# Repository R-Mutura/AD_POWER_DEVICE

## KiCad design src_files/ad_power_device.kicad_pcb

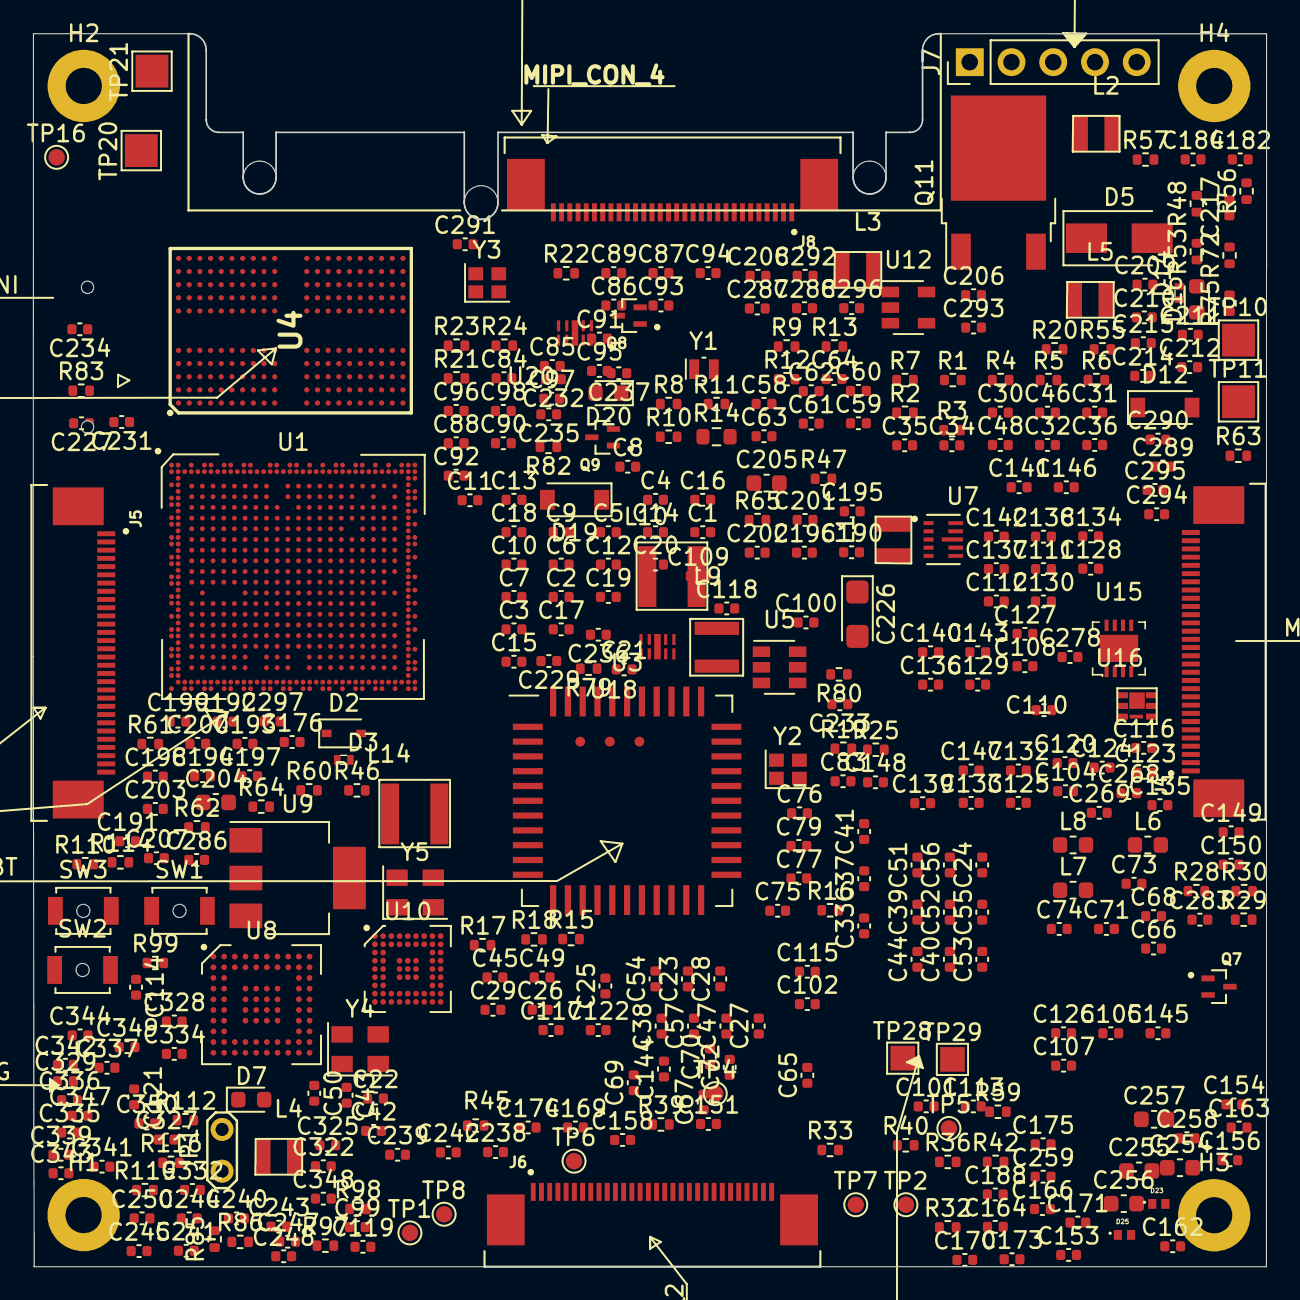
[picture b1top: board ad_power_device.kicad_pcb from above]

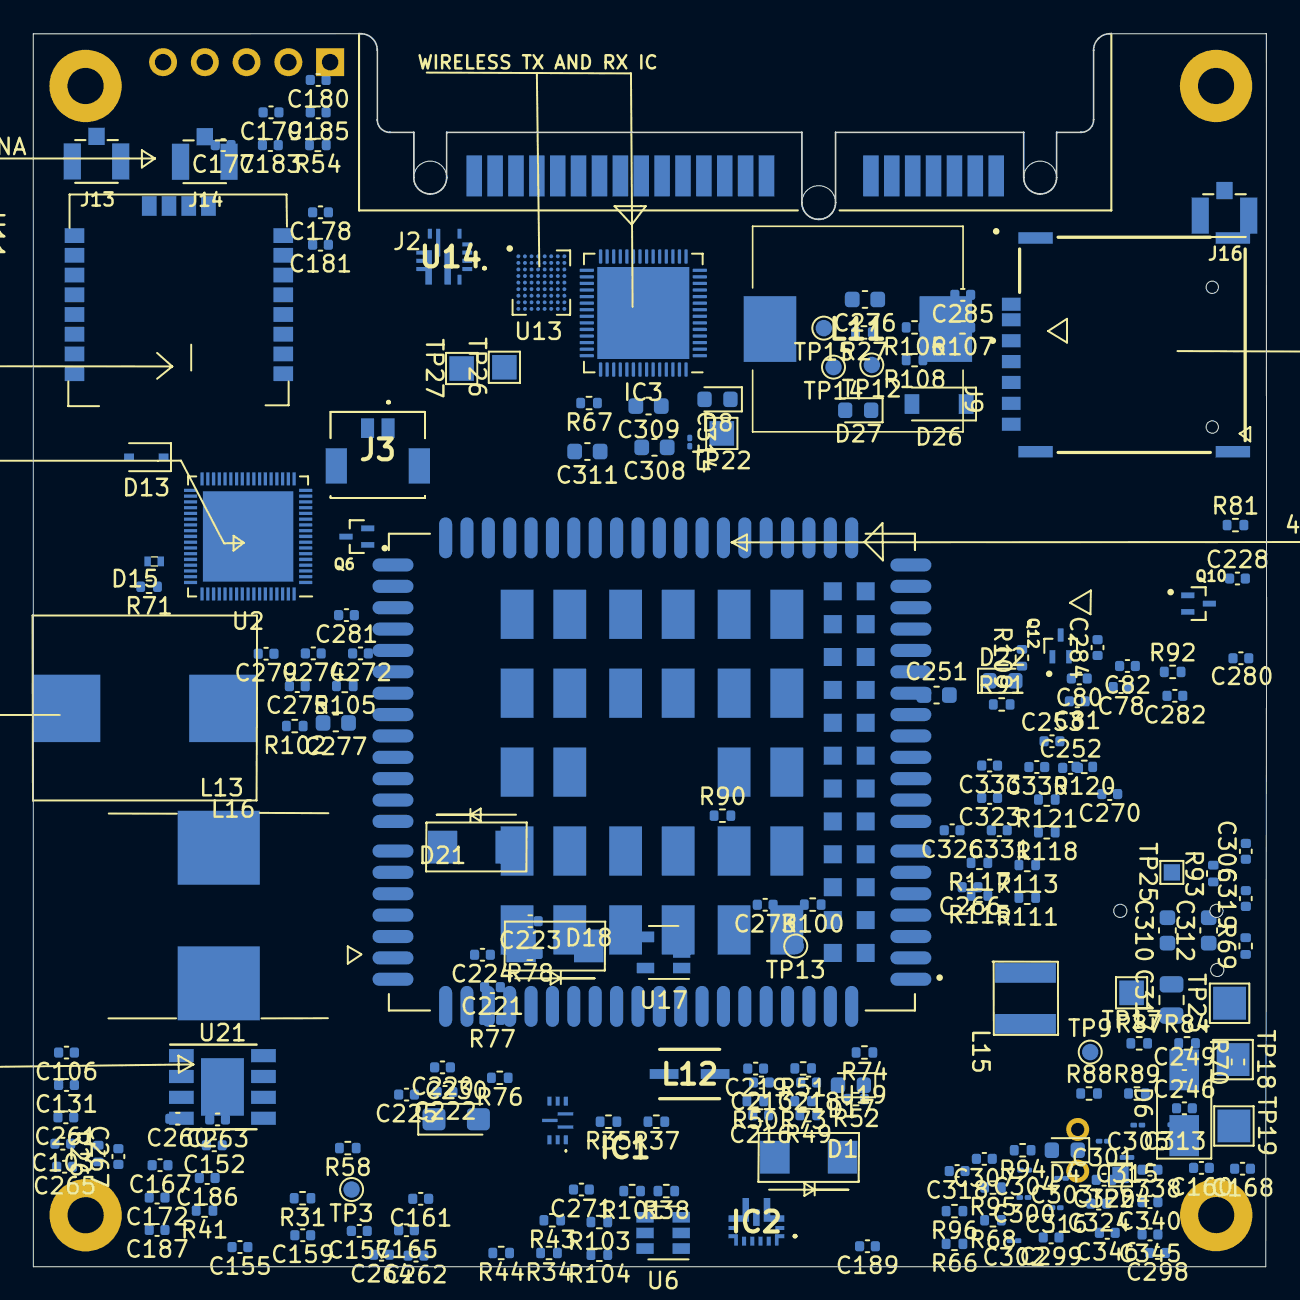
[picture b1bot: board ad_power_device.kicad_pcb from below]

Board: 2 copper layers, 75.0 x 75.0 mm, 593 parts (207 on the bottom side), 373 nets, no tracks yet.

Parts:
C1, C2, C5, C6, C15, C17, C18, C19, C21, C23, C24, C29, C30, C36, C48, C49, C99, C101, C122, C124, C149, C150, C222, C223, C224, C225, C283: 22uF; C_0402_1005Metric
C3, C4, C20, C31, C32, C35, C38, C39, C45, C46, C55, C79, C81, C96, C100, C102, C104, C106, C109, C131, C146, C148, C164, C165, C167, C169, C220, C221, C270, C280, C281, C282, C298, C306, C307, C332, C335, C339: 10uF; C_0402_1005Metric
C7, C10, C12, C13, C14, C16, C51, C83, C94, C95, C97, C107, C151, C152, C184, C186, C187, C239, C242, C279: 4.7uF; C_0402_1005Metric
C8, C9, C11, C63, C64, C78, C80, C82, C86, C87, C88, C89, C90, C91, C92, C93, C103, C105, C110, C112, C113, C114, C115, C116, C117, C118, C119, C120, C121, C123, C125, C126, C127, C128, C129, C130, C132, C133, C134, C135, C136, C137, C138, C139, C140, C141, C142, C143, C144, C145, C147, C157, C158, C159, C160, C161, C162, C163, C166, C168, C170, C171, C172, C173, C174, C175, C177, C183, C185, C188, C189, C190, C192, C193, C194, C195, C196, C197, C198, C199, C200, C201, C202, C208, C211, C212, C215, C216, C217, C218, C227, C231, C236, C238, C240, C241, C243, C244, C245, C250, C258, C259, C260, C261, C262, C263, C264, C265, C266, C267, C271, C278, C286, C287, C288, C289, C290, C291, C292, C293, C294, C297, C318, C319, C325, C329, C331, C344, C345, C346, C347: 100nF; C_0402_1005Metric
C22, C27, C28, C33, C34, C40, C41, C42, C43, C44, C47, C50, C52, C54, C61, C62, C67, C69, C70, C108, C111, C153, C154, C155, C156, C176, C206, C209, C210, C213, C214, C219, C252, C253, C295, C296, C322, C324, C326, C328: 1uF; C_0402_1005Metric
C25, C26, C53, C60: 100n; C_0402_1005Metric
C37, C56, C57: 10u; C_0402_1005Metric
C58, C59: 22pF; C_0402_1005Metric
C65: 10uF_10V; C_0402_1005Metric
C66, C68, C273: 2.2uF; C_0402_1005Metric
C71, C72: 100nF_10V; C_0402_1005Metric
C73, C74, C246, C247, C248, C249: 1nF_50V; C_0402_1005Metric
C75, C76: 12pF; C_0402_1005Metric
C77: 9pF; C_0402_1005Metric
C84, C85: 18pF; C_0402_1005Metric
C98, C336, C343: 1nF; C_0402_1005Metric
C178, C179: 220pF; C_0402_1005Metric
C180, C181: 180pF; C_0402_1005Metric
C182: 66pF; C_0402_1005Metric
C191, C203, C207: 0.1uF; C_0402_1005Metric
C204, C205, C310, C311, C312: 10uF; C_0603_1608Metric
C226, C230: 100uF; CP_EIA-3216-18_Kemet-A
C228, C232, C234, C235, C237: 33pF; C_0402_1005Metric
C229, C233: 10pF; C_0402_1005Metric
C251: 3200pF; C_0603_1608Metric
C254, C255: 47uF_10V; C_0603_1608Metric
C256, C257: 22uF_10V; C_0603_1608Metric
C268, C269: 27pF_50V; C_0402_1005Metric
C272: 100NF; C_0402_1005Metric
C274: 39nF; C_0402_1005Metric
C275: 82pF; C_0402_1005Metric
C276, C277: 22uF_16V; C_0603_1608Metric
C284, C285: 10nF; C_0402_1005Metric
C299: 4.7nF; C_0402_1005Metric
C300, C301: 22nF; C_01005_0402Metric
C302, C303, C304, C305, C313: 47nF; C_01005_0402Metric
C308, C309: 2.2uF; C_0603_1608Metric
C314, C315, C316: 100nF; C_01005_0402Metric
C317: 15uF; C_0805_2012Metric
C320: 100pF; C_0402_1005Metric
C323, C327, C330, C333, C334: 6.8nF; C_0402_1005Metric
C337, C338: 100nF_50V; C_0402_1005Metric
C340, C341, C349: 22nF_50V; C_0402_1005Metric
C342, C348, C350: 3.3nF; C_0402_1005Metric
D1, D18, D21: SS56; SMAG
D2, D13: 1N5819WS; D_SOD-323
D3, D14, D15: ESD5451R-2/TR; DFP1006-2L
D4, D7, D16, D17, D22: LED; LED_0603_1608Metric
D5, D6: SMAJ16A; D_SMA
D8: CDSU400B; D_0603_1608Metric
D12, D19, D26: SMF11A; D_SOD-123
D20, D27: LED_GREEN; LED_0603_1608Metric
D23, D25: ESD9X5VU; ESD9X5VU_DFN1006-2
H1, H2, H3, H4: MountingHole; MountingHole_2.2mm_M2_Pad
IC1: TPS62867RQYR; TPS62865RQYR
IC2: TPS61288RQQR
IC3: P9038; QFN-56-1EP_7x7mm_P0.4mm_EP5.6x5.6mm
J2: 5622-6309-ML; 3M_5622-6309-ML
J3: 205957-0271; 2059570271
J4, J5, J6, J8: 3-1734592-0; TE_3-1734592-0
J7: Conn_01x05_Male; PinHeader_1x05_P2.54mm_Vertical
J9: SIM8066-6-1-14-01-A_REVA; GCT_SIM8066-6-1-14-01-A_REVA
J13, J14, J16: U.FL-R-SMT-1(10); HRS_U.FL-R-SMT-1(10)
JP1: Jumper; TestPoint_2Pads_Pitch2.54mm_Drill0.8mm
L1, L2, L3, L4, L5: 470nH<50mOhm; 252010CDMCDDS-R47MC
L6: 120R_100MHz_2A; L_0603_1608Metric
L7, L8: 180R_100M_1.5A; L_0603_1608Metric
L9: 3.3uH_1.32A_0.08Ohm; SNR3015K-3R3M
L10, L14: 2.2uH; WPN4020H2R2MT
L11: RLF12560T2R7N110
L12: IHLP1212AEERR22M11; INDPM3630X150N
L13: 6uH; 7443550600
L15: 470nH; FNR4018SR47NT
L16: MWSA1004S-3R3MT
Q6, Q7, Q8, Q9, Q10, Q12: DTC143ZEBTL; SOTFL50P160X85-3N
Q11: IRFR9024NTRPBF; TO-252-2
R1, R2, R5, R71, R99: 100R; R_0402_1005Metric
R3, R4, R21, R31, R32, R54, R55, R58, R59, R72, R79, R80, R82, R83, R109: 0R; R_0402_1005Metric
R6, R7: 47K_1%; R_0402_1005Metric
R8, R9, R13, R92, R96, R97, R111, R118: 10K; R_0402_1005Metric
R10, R11, R12, R15, R16, R17, R18, R19, R73: 22R; R_0402_1005Metric
R14: 33K; R_0603_1608Metric
R20, R56, R106, R107, R108, R113, R114, R115: 4.7K; R_0402_1005Metric
R22: 240R_1%; R_0402_1005Metric
R23, R24: 120R_1%; R_0402_1005Metric
R25, R94, R102: 20K; R_0402_1005Metric
R26, R84, R89: 0.1R; R_0402_1005Metric
R27: 34K; R_0402_1005Metric
R28, R76, R93, R104, R105: 100K; R_0402_1005Metric
R29: 806K; R_0402_1005Metric
R30: 91K; R_0402_1005Metric
R33, R34, R35, R36: 1R_1%; R_0402_1005Metric
R37, R38, R39, R40, R41, R42, R43, R44: 2.2R_5%; R_0402_1005Metric
R45: 1.62K_1%; R_0402_1005Metric
R46, R48, R49, R50, R51, R52, R53, R60: 2.2K_5%; R_0402_1005Metric
R47, R61, R63: 2.2K_402; R_0402_1005Metric
R57, R62, R64, R74, R75, R90: 1K; R_0402_1005Metric
R65: 1KK; R_0402_1005Metric
R66, R67: 470R; R_0402_1005Metric
R68, R69, R70, R119: 47K; R_0402_1005Metric
R77: 205K; R_0402_1005Metric
R78: 6.8K_1%; R_0402_1005Metric
R81, R98, R121: 15K; R_0402_1005Metric
R85, R86, R87, R88: 10K_1%; R_0402_1005Metric
R91: 22.6R; R_0402_1005Metric
R95: 73.2K; R_0402_1005Metric
R100: 931K; R_0402_1005Metric
R101: 48.7K; R_0402_1005Metric
R103: 475K; R_0402_1005Metric
R110, R112, R117: 10M; R_0402_1005Metric
R116: 0.01R; R_0402_1005Metric
R120: 1.5K; R_0402_1005Metric
SW1: PWR_ON; SW_SPST_B3U-1000P-B
SW2: RESET BTN; SW_SPST_B3U-1000P-B
SW3: RECOVER BTN; SW_SPST_B3U-1000P-B
TP1: HDMI_TX_AVDD_0V9; TestPoint_Pad_D1.0mm
TP2: HDMI_TX_AVDD_1V8; TestPoint_Pad_D1.0mm
TP3: LVDS_TX0_AVDD_1V8; TestPoint_Pad_D1.0mm
TP4: LVDS_TX0_AVDD_0V9; TestPoint_Pad_D1.0mm
TP5: LVDS_TX1_AVDD_0V9; TestPoint_Pad_D1.0mm
TP6: LVDS_TX1_AVDD_1V8; TestPoint_Pad_D1.0mm
TP7: EDP_TX_AVDD_0V9; TestPoint_Pad_D1.0mm
TP8: EDP_TX_AVDD_1V8; TestPoint_Pad_D1.0mm
TP9: USB_OTG_ID; TestPoint_Pad_D1.0mm
TP10: bat+; TestPoint_Pad_2.0x2.0mm
TP11: bat-; TestPoint_Pad_2.0x2.0mm
TP12: VDD_CPU; TestPoint_Pad_D1.0mm
TP13: 3V3; TestPoint_Pad_D1.0mm
TP14: 12V; TestPoint_Pad_D1.0mm
TP15: VCC3V3_EXT; TestPoint_Pad_D1.0mm
TP16: 5V_VIN; TestPoint_Pad_D1.0mm
TP17: RX_COIL-; TestPoint_Pad_1.5x1.5mm
TP18: PWR_IN+; TestPoint_Pad_2.0x2.0mm
TP19: PWR_IN-; TestPoint_Pad_2.0x2.0mm
TP20, TP21: DBG_RXD; TestPoint_Pad_2.0x2.0mm
TP22: RX_COIL+; TestPoint_Pad_1.5x1.5mm
TP23: rx_vout; TestPoint_Pad_2.0x2.0mm
TP24: USB_D-; TestPoint_Pad_1.0x1.0mm
TP25: USB_D+; TestPoint_Pad_1.0x1.0mm
TP26: TX_COIL-; TestPoint_Pad_1.5x1.5mm
TP27: TX_COIL+; TestPoint_Pad_1.5x1.5mm
TP28: SPK-; TestPoint_Pad_1.5x1.5mm
TP29: SPK+; TestPoint_Pad_1.5x1.5mm
U1: RK3566; RK366_BGA-565_20x18_15.5x14.4mm
U2: RK809; QFN-68_EP_7x7_Pitch0.35mm
U3: AP6256; ap6256_QFN-44_12.5x12.5_Pitch0.9mm
U4: LPDDR4_32_IS43LQ32128A-062BLI; BGA200C65P12X22_1000X1450X85
U5, U6: TLV62569PDDCR; SOT-23-6
U7: TPS63802DLAR; VREG_TPS63802DLAR
U8: TC358779XBG
U9: ZLDO1117G12TA; SOT-223-3_TabPin2
U10: TC358860XBG
U11: NFC_VS1797SM; VS1797SM
U12: TLV71211DBVR; SOT-23-5
U13: STWLC68
U14: TPS56637RPAR
U15: 24AA64T-I/OT; WFDFN-8-1EP_3x3mm
U16: BRCS120N02ZJ
U17: SY6280AAAC; SOT-23-5
U18, U20: ESD5304D-TP
U19: EG25G; XCVR_EG25G
U21: SY6912A; Diodes_SO-8EP
Y1: 32.768KHz; Crystal_SMD_MicroCrystal_CM9V-T1A-2Pin_1.6x1.0mm
Y2: 37.4MHz_10PPM; Crystal_SMD_2016-4Pin_2.0x1.6mm
Y3: 24MHz/10ppm; Crystal_SMD_2016-4Pin_2.0x1.6mm
Y4, Y5: ASE-27.000MHZ-LR-T(27MHz); Crystal_SMD_EuroQuartz_MT-4Pin_3.2x2.5mm

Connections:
+1V1: C208.1, C286.1, C288.1, C291.1, C292.1, C296.1, R62.1, U10.A8, U10.G1, U10.G9, U10.J1, U10.J5, U12.5
+1V2: C194.1, C195.1, C196.1, C199.1, C200.1, C201.1, C202.1, C205.1, C293.1, C294.1, U8.A1, U8.A3, U8.A8, U8.D10, U8.H1, U8.K1, U8.K10, U9.3, U10.A1, U10.A2
+3V3: C22.1, C27.1, C28.1, C33.1, C34.1, C38.1, C39.1, C62.2, C79.1, C80.1, C107.1, C176.1, C192.1, C193.1, C197.1, C198.1, C204.1, C206.1, C222.1, C223.1, C224.1, C270.1, C271.1, C279.1, C287.1, C295.1, C297.1, D2.2, D16.2, D17.2, IC1.8, IC1.9, IC2.6, IC2.7, IC2.15, L11.1, L12.2, R47.1, R61.1, R63.1, R103.2, TP13.1, U2.4, U2.10, U2.11, U2.22, U2.24, U2.30, U2.45, U2.54, U2.57, U2.66, U3.9, U5.4, U6.4, U8.B1, U8.G1, U8.G5, U8.K2, U8.K4, U8.K7, U9.1, U10.A9, U12.1, U12.3, U17.5, Y4.1, Y4.4, Y5.1, Y5.4
+5V: C164.1, C165.1, C166.1, C168.1, C170.1, C172.1, C174.1, C175.1, C185.1, C220.1, C221.1, C254.1, C255.1, C256.1, C257.1, C258.1, D1.1, D18.1, D21.2, IC1.3, IC1.4, IC3.14, IC3.15, IC3.16, J2.P7, J2.P8, J2.P9, J4.1, J4.2, J4.3, J5.1, J5.2, J5.3, J6.1, J6.2, J6.3, J7.1, J8.1, J8.2, J8.3, L6.1, L16.2, R13.1, R76.2, R93.1, R94.1, R95.1, TP16.1, TP18.1, U16.1, U16.2, U16.5, U16.6
+12V: C276.1, C277.1, IC2.5, IC2.14, J2.P13, J2.P14, J2.P15, R100.1, TP14.1
/4G_MODEM_ON: Q8.1, U1.AR10
/4G_MODEM_RESETn: Q9.1, U1.AP10
/4G_MODULE/1.8V_local_ldo: R106.2, R107.1, R108.1, U19.7
/4G_MODULE/ANT_GNSS_GPS: R79.2, U19.47
/4G_MODULE/ANT_MAIN: R80.2, U19.49
/4G_MODULE/DBG_RXD: TP20.1, U19.11
/4G_MODULE/DBG_TXD: TP21.1, U19.12
/4G_MODULE/Net_status: Q12.1, U19.6
/4G_MODULE/PWR_EN: C284.1, Q8.3, U19.21
/4G_MODULE/RESET_n: C285.1, Q9.3, U19.20
/4G_MODULE/Status_indicator: Q10.1, U19.61
/4G_MODULE/USB_BOOT: D26.K, JP1.2, U19.115
/4G_MODULE/USM1_CLK: R83.2, U19.16, U20.3
/4G_MODULE/USM1_DATA: R109.2, U19.15, U20.4
/4G_MODULE/USM1_RST: R82.2, U19.17, U20.2
/4G_MODULE/USM1_VDD: C236.2, J9.C1, R81.2, U19.14, U20.1
/4G_MODULE_SCL: R107.2, U19.42
/4G_MODULE_SDA: R108.2, U19.41
/4G_MODULE_USB_D+: U18.3, U19.69
/4G_MODULE_USB_D-: U18.4, U19.70
/5W_QI_PWR_OUTPUT/GPIO1: C342.1, C348.1, C349.1, IC3.8, R119.1
/5W_QI_PWR_OUTPUT/LDO5V: C322.1, C324.1, IC3.19, IC3.21, IC3.22, R111.1, U15.2, U15.8
/ANTRDR_n: R54.1, U11.19
/ANTRDR_p: R55.1, U11.18
/AP6256_WIFI_BT/ANT: C77.1, U3.2
/AP6256_WIFI_BT/LPO: C78.1, R15.1, U3.24
/AP6256_WIFI_BT/XTAL_IN: C75.1, U3.10, Y2.3
/AP6256_WIFI_BT/XTAL_OUT: C76.1, U3.11, Y2.1
/AP_READY: U1.AR9, U19.2
/BATTERY_CHARGER/FB: R29.2, R30.1, U7.4
/BL_EN_GPIO0_C0_DISPLAY_TWO: J4.11, U1.A29
/BL_EN_GPIO1_B7_DISPLAY_ONE: J6.11, U1.B29
/BT_WAKE_HOST_H_GPIO2_C0: U1.A37, U3.37
/GPIO1_B4_DISPLAY_ONE: J6.5, U1.A32
/GPIO1_C2_u_DISPLAY_TWO: J4.5, U1.B30
/HDMITX_SCL: U1.AR12, U8.J1
/HDMITX_SDA: U1.AP11, U8.J2
/HOST_WAKE_BT_H_GPIO2_C1: U1.B36, U3.6, U3.39
/I2C0_SCL_PMIC: R50.2, U1.AJ37, U2.1
/I2C0_SDA_PMIC: R51.2, U2.2
/I2C2_SCL_M0_TP: J4.8, J5.8, J6.8, J8.8, R52.2
/I2C2_SDA_M0_TP: J4.7, J5.7, J6.7, J8.7, R53.2
/I2S1_LRCK_TX_M0_RK809: U1.B24, U2.14
/I2S1_SCLK_TX_M0_RK809: U1.B23, U2.15
/I2S1_SDO0_M0_RK809: U1.B25, U2.17
/I2S2_SCLK_TX_M0: R17.1, U1.C37
/I2S2_SDI_M0: R18.1, U1.D37
/LCD_1_EN_GPIO1_B5_C7: J6.9, U1.B27
/LCD_RST_L_GPIO0_C2: J5.13, U1.AM37
/LCD_RST_L_GPIO1_C0_DISPLAY_ONE: J6.13, U1.B33
/NFC_REQ: U1.AG2, U11.3
/NFC_SCL: R56.1, U1.AE2, U11.5
/NFC_SDA: R20.1, U1.AF2, U11.4
/NFC_WAKE: R57.1, U11.2
/PMIC_32KOUT_WIFI: R8.2, R10.2, R15.2
/PMIC_EXT_EN: R12.2, U2.60, U17.4
/RECOVER: C246.1, R85.2, SW3.1
/RESETn: C60.2, C86.1, R9.2, R11.2, R21.1, U2.67
/RF1: C180.2, C182.1, J3.1
/RF2: C181.2, C182.2, J3.2
/RK809_CODEC/SPK_MINI_N: C74.1, L7.2, TP28.1
/RK809_CODEC/SPK_MINI_P: C73.1, L8.2, TP29.1
/RK809_IC_DCDC/FB1: R3.2, U2.13
/RK809_IC_DCDC/FB3: R6.2, R7.1, U2.27
/RK809_IC_DCDC/FB5: R4.1, U2.59
/RK809_IC_DCDC/SW1: L2.2, U2.12
/RK809_IC_DCDC/SW2: L1.2, U2.9
/RK809_IC_DCDC/SW3: L5.2, U2.25
/RK809_IC_DCDC/SW4: L4.2, U2.65
/RK809_IC_DCDC/SW5: L3.2, U2.53
/RK890_IC_AUXILLARY/PMIC_PWRON: C63.2, R99.2, U2.52
/RK890_IC_AUXILLARY/RST_KEY: R11.1, SW2.1
/RK3566_LPDDR3/I2C1_SCL: R48.2, U1.AK37
/RK3566_LPDDR3/I2C1_SDA: R49.2, U1.AM38
/RK3566_LPDDR3/LPDDR4_A0_A: U1.C2, U4.H2
/RK3566_LPDDR3/LPDDR4_A0_B: U1.A9, U4.R2
/RK3566_LPDDR3/LPDDR4_A1_A: U1.C1, U4.J2
/RK3566_LPDDR3/LPDDR4_A1_B: U1.B9, U4.P2
/RK3566_LPDDR3/LPDDR4_A5_B: U1.B8, U4.P11
/RK3566_LPDDR3/LPDDR4_CKE0_A: U1.B4, U4.J4
/RK3566_LPDDR3/LPDDR4_CLKN_A: U1.A5, U4.J9
/RK3566_LPDDR3/LPDDR4_CLKN_B: U1.B7, U4.P9
/RK3566_LPDDR3/LPDDR4_CLKP_A: U1.B5, U4.J8
/RK3566_LPDDR3/LPDDR4_CLKP_B: U1.A7, U4.P8
/RK3566_LPDDR3/LPDDR4_CS0n_A: U1.B3, U4.H4
/RK3566_LPDDR3/LPDDR4_DQ0_A: U1.G2, U4.B2
/RK3566_LPDDR3/LPDDR4_DQ0_B: U1.B12, U4.AA2
/RK3566_LPDDR3/LPDDR4_DQ1_A: U1.F2, U4.C2
/RK3566_LPDDR3/LPDDR4_DQ1_B: U1.B10, U4.Y2
/RK3566_LPDDR3/LPDDR4_DQ2_A: U1.F1, U4.E2
/RK3566_LPDDR3/LPDDR4_DQ3_A: U1.E1, U4.F2
/RK3566_LPDDR3/LPDDR4_DQ4_A: U1.M2, U4.F4
/RK3566_LPDDR3/LPDDR4_DQ4_B: U1.B13, U4.U4
/RK3566_LPDDR3/LPDDR4_DQ5_A: U1.K1, U4.E4
/RK3566_LPDDR3/LPDDR4_DQ6_A: U1.K2, U4.C4
/RK3566_LPDDR3/LPDDR4_DQ8_A: U1.P2, U4.B11
/RK3566_LPDDR3/LPDDR4_DQ8_B: U1.B19, U4.AA11
/RK3566_LPDDR3/LPDDR4_DQ9_A: U1.R1, U4.C11
/RK3566_LPDDR3/LPDDR4_DQ9_B: U1.A19, U4.Y11
/RK3566_LPDDR3/LPDDR4_DQ10_A: U1.R2, U4.E11
/RK3566_LPDDR3/LPDDR4_DQ10_B: U1.A20, U4.V11
/RK3566_LPDDR3/LPDDR4_DQ11_A: U1.T2, U4.F11
/RK3566_LPDDR3/LPDDR4_DQ11_B: U1.B20, U4.U11
/RK3566_LPDDR3/LPDDR4_DQ12_A: U1.M1, U4.F9
/RK3566_LPDDR3/LPDDR4_DQ12_B: U1.A15, U4.U9
/RK3566_LPDDR3/LPDDR4_DQ13_B: U1.B15, U4.V9
/RK3566_LPDDR3/LPDDR4_DQ15_B: U1.B16, U4.AA9
/RK3566_LPDDR3/LPDDR4_DQS0N_A: U1.H1, U4.E3
/RK3566_LPDDR3/LPDDR4_DQS0N_B: U1.A12, U4.V3
/RK3566_LPDDR3/LPDDR4_DQS0P_A: U1.H2, U4.D3
/RK3566_LPDDR3/LPDDR4_DQS0P_B: U1.A13, U4.W3
/RK3566_LPDDR3/LPDDR4_DQS1N_A: U1.N2, U4.E10
/RK3566_LPDDR3/LPDDR4_DQS1N_B: U1.B17, U4.V10
/RK3566_LPDDR3/LPDDR4_DQS1P_A: U1.N1, U4.D10
/RK3566_LPDDR3/LPDDR4_DQS1P_B: U1.A17, U4.W10
/RK3566_LPDDR3/LPDDR4_ODT0_CA_A: U1.E2, U4.G2
/RK3566_LPDDR3/LPDDR4_ODT0_CA_B: U1.A10, U4.T2
/RK3566_LPDDR3/LPDDR4_RESETn: C98.1, U4.T11
/RK3566_LPDDR3/UART2_TX_M0_DEBUG: D12.K, R71.1
/RK3566_PART_C/1G17: C189.1, R59.1, TP8.1
/RK3566_PART_C/1H17: C188.1, R58.1, TP7.1
/RK3566_PART_C/1N10: C161.1, R35.1, TP5.1
/RK3566_PART_C/1N14: C157.1, R31.1, TP1.1
/RK3566_PART_C/1P11: C160.1, R34.1, TP4.1
/RK3566_PART_C/1P12: C159.1, R33.1, TP3.1
/RK3566_PART_C/1P13: C158.1, R32.1, TP2.1
/RK3566_PART_C/1R10: C162.1, R36.1, TP6.1
/RK3566_PART_C/BL_EN_GPIO0_C0_DISPLAY_THREE: J8.11, U1.AP3
/RK3566_PART_C/DP TO MIPI/DSIODM_MIPI_C-: J8.23, U10.D2
/RK3566_PART_C/DP TO MIPI/DSIODM_MIPI_D0-: J8.17, U10.B2
/RK3566_PART_C/DP TO MIPI/DSIODM_MIPI_D1-: J8.20, U10.C2
/RK3566_PART_C/DP TO MIPI/DSIODM_MIPI_D2-: J8.26, U10.E2
/RK3566_PART_C/DP TO MIPI/DSIODM_MIPI_D3-: J8.29, U10.F2
/RK3566_PART_C/DP TO MIPI/DSIODP_MIPI_C+: J8.22, U10.D1
/RK3566_PART_C/DP TO MIPI/DSIODP_MIPI_D0+: J8.16, U10.B1
/RK3566_PART_C/DP TO MIPI/DSIODP_MIPI_D1+: J8.19, U10.C1
/RK3566_PART_C/DP TO MIPI/DSIODP_MIPI_D2+: J8.25, U10.E1
/RK3566_PART_C/DP TO MIPI/DSIODP_MIPI_D3+: J8.28, U10.F1
/RK3566_PART_C/EDP_TX_D0+: U1.J37, U10.J8
/RK3566_PART_C/EDP_TX_D1+: U1.K38, U10.J6
/RK3566_PART_C/EDP_TX_D1-: U1.K37, U10.H6
/RK3566_PART_C/EDP_TX_D2+: U1.M37, U10.J4
/RK3566_PART_C/EDP_TX_D2-: U1.M38, U10.H4
/RK3566_PART_C/EDP_TX_D3+: U1.N37, U10.J2
/RK3566_PART_C/EDP_TX_D3-: U1.N38, U10.H2
/RK3566_PART_C/GPIO1_C2_u_DISPLAY_THREE: J8.5, U1.AP9
/RK3566_PART_C/HDMI_TX0N_PORT-: R42.2, U8.D2
/RK3566_PART_C/HDMI_TX0P_PORT+: R41.2, U8.D1
/RK3566_PART_C/HDMI_TX1N_PORT-: R40.2, U8.E2
/RK3566_PART_C/HDMI_TX1P_PORT+: R38.2, U8.E1
/RK3566_PART_C/HDMI_TX2N_PORT-: R39.2, U8.F2
/RK3566_PART_C/HDMI_TX2P_PORT+: R37.2, U8.F1
/RK3566_PART_C/HDMI_TXCLKN_PORT-: R44.2, U8.C2
/RK3566_PART_C/HDMI_TXCLKP_PORT+: R43.2, U8.C1
/RK3566_PART_C/HDMI_TX_HPDIN: C163.1, R64.2
/RK3566_PART_C/INT_hdmi_to_mipi: U1.AR7, U8.J4
/RK3566_PART_C/LCD_3_ENGPIO1_C3_u_TO_DISPLAY: J8.9, U1.AR4
/RK3566_PART_C/LCD_BL_PWM12_M0_DISPLAY_ONE: J6.12, U1.AP5
/RK3566_PART_C/MCDP_I2C_SCL: R60.2, U1.AP6, U8.J5, U10.C9
/RK3566_PART_C/MCDP_I2C_SDA: R46.2, U8.K5, U10.C8
/RK3566_PART_C/MIPI_C+: J4.22, U8.C9
/RK3566_PART_C/MIPI_C-: J4.23, U8.C10
/RK3566_PART_C/MIPI_D0+: J4.16, U8.F9
/RK3566_PART_C/MIPI_D0-: J4.17, U8.F10
/RK3566_PART_C/MIPI_D1+: J4.19, U8.E9
/RK3566_PART_C/MIPI_D1-: J4.20, U8.E10
/RK3566_PART_C/MIPI_D2+: J4.25, U8.B9
/RK3566_PART_C/MIPI_D2-: J4.26, U8.B10
/RK3566_PART_C/MIPI_D3+: J4.28, U8.A9
/RK3566_PART_C/MIPI_D3-: J4.29, U8.A10
/RK3566_PART_C/MIPI_DSI_TX0_D0N-: J5.17, U1.AR30
/RK3566_PART_C/MIPI_DSI_TX0_D0P+: J5.16, U1.AP30
/RK3566_PART_C/MIPI_DSI_TX0_D1N-: J5.20, U1.AP29
/RK3566_PART_C/MIPI_DSI_TX0_D1P+: J5.19, U1.AR29
/RK3566_PART_C/MIPI_DSI_TX0_D2N-: J5.26, U1.AR27
/RK3566_PART_C/MIPI_DSI_TX0_D2P+: J5.25, U1.AP27
/RK3566_PART_C/MIPI_DSI_TX0_D3N-: J5.29, U1.AP26
/RK3566_PART_C/MIPI_DSI_TX1_D0+: J6.16, U1.AP24
/RK3566_PART_C/MIPI_DSI_TX1_D0-: J6.17, U1.AR24
/RK3566_PART_C/MIPI_DSI_TX1_D1-: J6.20, U1.AP23
/RK3566_PART_C/MIPI_DSI_TX1_D2+: J6.25, U1.AP21
/RK3566_PART_C/MIPI_DSI_TX1_D2-: J6.26, U1.AR21
/RK3566_PART_C/MIPI_DSI_TX1_D3-: J6.29, U1.AP20
/RK3566_PART_C/TP_INT_GPIO0_A5_DISPLAY_THREE: J8.10, U1.AP4
/RK3566_PART_C/VCC5V_HDMI_TX: D2.1, D3.1, U8.J3
/SATA1_RX+: J2.S5, J2.S6, U1.V37, U1.V38
/SATA1_TX+: J2.S2, U1.W37
/SDMMC1_CLK: U1.B37, U3.16
/SDMMC1_CMD: U1.B35, U3.17
/TP_INT_GPIO0_A5: J5.10, U1.AG37
/TP_INT_GPIO0_A5_DISPLAY_TWO: J4.10, U1.A27
/TP_INT_GPIO1_B6_DISPLAY_ONE: J6.10, U1.B32
/TP_RST_L_GPIO1_C2_DISPLAY_ONE: J6.14, U1.A30
/UART1_CTSn_M0: U1.G37, U3.41
/UART1_RTSn_M0: U1.F37, U3.44
/UART1_TX_M0: U1.F38, U3.42
/USB)C_OTG_PWR_IN/COIL+: C313.1, C314.1, C315.1, C316.1, TP22.1
/USB)C_OTG_PWR_IN/COIL-: C301.1, C304.1, C305.1, TP17.1, U13.A2, U13.A3, U13.B2, U13.B3
/USB)C_OTG_PWR_IN/v1v8: C309.1, R67.1, R68.1, R69.1, R70.1, U13.G5, U13.G8, U13.J6
/USB_OTG0_D+: D23.1, TP25.1, U1.R37
/USB_OTG0_D-: D25.1, TP24.1, U1.R38
/USB_OTG0_VBUSDET: R97.1, R98.1
/WIFI_WAKE_HOST_H_GPIO2_B2: U1.B34, U3.13
GND: C1.2, C2.2, C3.2, C4.2, C10.2, C11.2, C12.2, C13.2, C14.2, C15.2, C16.2, C17.2, C18.2, C19.2, C20.2, C21.2, C22.2, C23.2, C24.2, C27.2, C28.2, C29.2, C30.2, C31.2, C32.2, C33.2, C34.2, C35.2, C36.2, C37.2, C38.2, C39.2, C40.2, C41.2, C42.2, C43.2, C44.2, C45.2, C46.2, C47.2, C48.2, C49.2, C50.2, C51.2, C52.2, C54.2, C55.2, C56.2, C57.2, C58.2, C59.2, C60.1, C61.2, C62.1, C63.1, C64.1, C65.2, C67.2, C68.2, C69.2, C70.2, C73.2, C74.2, C75.2, C76.2, C78.2, C79.2, C80.2, C81.2, C82.2, C83.2, C84.2, C85.2, C86.2, C87.2, C88.2, C89.2, C90.2, C91.2, C92.2, C93.2, C94.2, C95.2, C96.2, C97.2, C98.2, C99.2, C100.2, C101.2, C102.2, C103.2, C104.2, C105.2, C106.2, C107.2, C108.2, C109.2, C110.2, C111.2, C112.2, C113.2, C114.2, C115.2, C116.2, C117.2, C118.2, C119.2, C120.2, C121.2, C122.2, C123.2, C124.2, C125.2, C126.2, C127.2, C128.2, C129.2, C130.2, C131.2, C132.2, C133.2, C134.2, C135.2, C136.2, C137.2, C138.2, C139.2, C140.2, C141.2, C142.2, C143.2, C144.2, C145.2, C146.2, C147.2, C148.2, C149.2, C150.2, C151.2, C152.2, C153.2, C154.2, C155.2, C156.2, C157.2, C158.2, C159.2, C160.2, C161.2, C162.2, C163.2, C164.2, C165.2, C166.2, C167.2, C168.2, C169.2, C170.2, C171.2, C172.2, C173.2, C174.2, C175.2, C176.2, C177.2, C178.2, C179.1, C183.2, C184.2, C185.2, C186.2, C187.2, C188.2, C189.2, C190.2, C191.2, C192.2, C193.2, C194.2, C195.2, C196.2, C197.2, C198.2, C199.2, C200.2, C201.2, C202.2, C203.2, C204.2, C205.2, C206.2, C207.2, C208.2, C209.2, C210.2, C211.2, C212.2, C213.2, C214.2, C215.2, C216.2, C217.2, C218.2, C219.2, C220.2, C221.2, C222.2, C223.2, C224.2, C225.2, C226.2, C227.2, C228.2, C229.2, C230.2, C231.2, C232.2, C233.2, C234.2, C235.2, C236.1, C237.2, C238.2, C239.2, C240.2, C241.2, C242.2, C243.2, C244.2, C245.2, C246.2, C247.2, C248.2, C249.2, C250.2, C251.2, C252.2, C253.2, C254.2, C255.2, C256.2, C257.2, C258.2, C259.2, C260.2, C261.2, C262.2, C263.2, C264.2, C265.2, C266.2, C267.2, C268.1, C269.1, C270.2, C271.2, C273.2, C274.2, C275.2, C276.2, C277.2, C278.2, C279.2, C280.2, C281.2, C282.2, C283.2, C284.2, C285.2, C286.2, C287.2, C288.2, C289.2, C290.2, C291.2, C292.2, C293.2, C294.2, C295.2, C296.2, C297.2, C298.2, C306.2, C307.2, C308.2, C309.2, C310.2, C311.2, C312.2, C317.2, C318.2, C322.2, C323.2, C325.2, C326.2, C327.2, C328.2, C330.2, C331.2, C332.2, C333.2, C335.2, C336.2, C339.2, C340.2, C341.2, C343.2, C348.2, C350.2, D3.2, D7.1, D12.A, D14.2, D15.2, D19.A, D23.2, D25.2, D26.A, IC1.1, IC1.2, IC2.3, IC2.10, IC2.13, IC3.1, IC3.17, IC3.26, IC3.27, IC3.28, IC3.29, IC3.42, IC3.43, IC3.44, IC3.45, IC3.54, IC3.56, IC3.57, J2.P4, J2.P5, J2.P6, J2.P10, J2.P12, J2.S1, J2.S4, J2.S7, J3.MP1, J3.MP2, J4.4, J4.15, J4.18, J4.21, J4.24, J4.27, J4.30, J4.S1, J4.S2, J5.4, J5.15, J5.18, J5.21, J5.24, J5.27, J5.30, J5.S1, J5.S2, J6.4, J6.15, J6.18, J6.21, J6.24, J6.27, J6.30, J6.S1, J6.S2, J7.2, J8.4, J8.15, J8.18, J8.21, J8.24, J8.27, J8.30, J8.S1, J8.S2, J9.C5, J9.CD, J9.G1, J9.G2, J9.G3, J9.G4, J13.1, J13.3, J14.1, J14.3, J16.1, J16.3, Q6.2, Q7.2, Q8.2, Q9.2, Q10.2, Q12.2, R7.2, R12.1, R14.2, R30.2, R45.2, R65.2, R72.2, R77.2, R78.2, R92.2, R96.2, R98.2, R101.2, R105.2, R110.2, R117.2, R119.2, R121.2, SW1.2, SW2.2, SW3.2, TP11.1, TP19.1, U1.A1, U1.A2, U1.A38, U1.AA2, U1.AC37, U1.AD2, U1.AE37, U1.AH37, U1.AL37, U1.AP2, U1.AP8, U1.AP13, U1.AP16, U1.AP19, U1.AP22, U1.AP25, U1.AP28, U1.AP31, U1.AP34, U1.AP37, U1.AR1, U1.AR38, U1.B1, U1.B2, U1.B6, U1.B11, U1.B14, U1.B18, U1.B21, U1.B28, U1.B31, U1.D2, U1.E37, U1.H37, U1.J2, U1.L2, U1.L37, U1.P37, U1.U2, U1.U37, U1.W2, U1.Y37, U2.47, U2.56, U2.62, U2.63, U2.69, U3.1, U3.3, U3.20, U3.31, U3.33, U3.36, U4.A3, U4.A10, U4.AB3, U4.AB5, U4.AB8, U4.AB10, U4.C1, U4.C5, U4.C8, U4.C12, U4.D2, U4.D4, U4.D9, U4.D11, U4.E1, U4.E5, U4.E8, U4.E12, U4.G1, U4.G3, U4.G5, U4.G8, U4.G10, U4.G12, U4.J1, U4.J3, U4.J10, U4.J12, U4.K2, U4.K4, U4.K9, U4.K11, U4.V1, U4.V5, U4.V8, U4.V12, U4.W2, U4.W4, U4.W9, U4.W11, U4.Y1, U4.Y5, U4.Y8, U4.Y12, U5.2, U6.2, U7.2, U7.3, U7.8, U8.A7, U8.B2, U8.B3, U8.B4, U8.B5, U8.B6, U8.B8, U8.D4, U8.D5, U8.D6, U8.D7, U8.D9, U8.E4, U8.E5, U8.E6, U8.E7, U8.F4, U8.F5, U8.F6, U8.F7, U8.G2, U8.G4, U8.G6, U8.G7, U8.G9, U8.J8, U9.2, U10.B9, U10.D4, U10.D5, U10.D6, U10.E4, U10.E5, U10.E6, U10.F4, U10.G2, U10.H1, U10.H3, U10.H5, U10.H7, U11.1, U11.8, U11.10, U11.13, U11.16, U11.17, U11.20, U12.2, U13.A1, U13.A8, U13.B1, U13.B8, U13.C4, U13.C5, U13.D3, U13.D4, U13.E4, U13.E5, U13.F3, U13.F4, U13.F5, U13.F6, U13.G1, U13.G2, U13.G3, U13.G4, U13.G6, U13.G7, U13.H3, U13.H4, U13.H5, U13.H6, U13.H7, U13.J5, U14.3, U14.9, U14.10, U15.1, U15.3, U15.4, U17.2, U18.5, U19.8, U19.9, U19.10, U19.19, U19.22, U19.36, U19.46, U19.48, U19.50, U19.51, U19.52, U19.53, U19.54, U19.56, U19.72, U19.85, U19.86, U19.87, U19.88, U19.89, U19.90, U19.91, U19.92, U19.93, U19.94, U19.95, U19.96, U19.97, U19.98, U19.99, U19.100, U19.101, U19.102, U19.103, U19.104, U19.105, U19.106, U19.107, U19.108, U19.109, U19.110, U19.111, U19.112, U20.5, U21.9, Y2.2, Y2.4, Y3.2, Y3.4, Y4.2, Y5.2
unnamed: C5.2, C8.2
unnamed: C6.2, C7.2, C9.2
unnamed: C58.1, U2.50, Y1.1
unnamed: C59.1, U2.51, Y1.2
unnamed: C61.1, U2.46
unnamed: C64.2, R13.2, R14.1, U2.61
unnamed: C65.1, L6.2, U2.33
unnamed: C66.1, U2.36
unnamed: C66.2, U2.37
unnamed: C67.1, U2.38
unnamed: C68.1, U2.35
unnamed: C69.1, U2.48
unnamed: C70.1, U2.44
unnamed: C77.2, J16.2
unnamed: C83.1, L9.2, U3.23
unnamed: C84.1, U1.AD38, Y3.3
unnamed: C85.1, U1.AD37, Y3.1
unnamed: C105.1, R25.1, U5.1
unnamed: C150.1, C283.1, D1.2, R28.1, R29.1, U7.6
unnamed: C178.1, C180.1, R55.2
unnamed: C179.2, C181.1, R54.2
unnamed: C191.1, R47.2, U8.K6
unnamed: C203.1, R61.2, U8.A2
unnamed: C207.1, R63.2, U10.B8
unnamed: C234.1, J9.C7, R81.1, R109.1
unnamed: C235.1, J9.C3, R83.1
unnamed: C237.1, J9.C2, R82.1
unnamed: C247.1, R86.2
unnamed: C248.1, R87.2
unnamed: C249.1, R88.2
unnamed: C251.1, U21.1
unnamed: C252.1, D21.1, R90.1, U21.8
unnamed: C253.1, Q11.3, R91.1, TP10.1, U21.3
unnamed: C71.1, C268.2, U2.42
unnamed: C72.1, C269.2, U2.43
unnamed: C272.1, IC2.4, IC2.9, L11.2
unnamed: C272.2, IC2.8
unnamed: C273.1, IC2.11
unnamed: C274.1, R27.2
unnamed: C275.1, IC2.2, R27.1
unnamed: C278.1, R102.1, U6.1
unnamed: C298.1, C299.2, C306.1, C307.1, R66.2, U13.A4, U13.A5, U13.B4, U13.B5, U13.C3
unnamed: C299.1, U13.E8
unnamed: C300.1, C302.1, C303.1, C313.2, C314.2, C315.2, C316.2, U13.A6, U13.A7, U13.B6, U13.B7
unnamed: C300.2, U13.D8
unnamed: C301.2, U13.D7
unnamed: C302.2, U13.C8
unnamed: C303.2, U13.E7
unnamed: C304.2, U13.C1
unnamed: C305.2, U13.C7
unnamed: C308.1, U13.E6, U13.F7
unnamed: C319.1, U14.7
unnamed: C319.2, L16.1, U14.6
unnamed: C320.1, R95.2, R96.1, U14.2
unnamed: C320.2, R94.2
unnamed: C323.1, IC3.47, R110.1, U16.3
unnamed: C325.1, C327.1, C328.1, C329.1, IC3.18, IC3.50, R116.1, U16.4
unnamed: C326.1, IC3.20, R112.1
unnamed: C329.2, C330.1, C331.1, C332.1, C335.1, C339.1, IC3.34, IC3.35, IC3.36, IC3.37, IC3.49, R116.2
unnamed: C333.1, IC3.24
unnamed: C334.1, IC3.52
unnamed: C334.2, C343.1, R118.2
unnamed: C336.1, IC3.48
unnamed: C337.1, C341.1, C344.1, C345.1, C346.1, C347.1, IC3.30, IC3.31, IC3.32, IC3.33
unnamed: C337.2, IC3.25
unnamed: C338.1, IC3.46
unnamed: C338.2, C340.1, IC3.38, IC3.39, IC3.40, IC3.41, TP27.1
unnamed: C342.2, IC3.55, R118.1
unnamed: C344.2, C345.2, C346.2, C347.2, D8.2, TP26.1
unnamed: C349.2, C350.1, R120.2, R121.1
unnamed: D4.1, U13.H2
unnamed: D4.2, R67.2
unnamed: D7.2, R114.2
unnamed: D8.1, R120.1
unnamed: D13.1, R73.1
unnamed: D14.1, R71.2
unnamed: D15.1, R73.2
unnamed: D16.1, R74.1
unnamed: D17.1, R75.1
unnamed: D20.1, Q10.3
unnamed: D22.1, U21.6
unnamed: D22.2, R90.2
unnamed: D27.1, Q12.3
unnamed: IC1.5, R76.1
unnamed: IC1.6, R77.1
unnamed: IC1.7, L12.1
unnamed: IC2.1, IC2.12, R100.2, R101.1
unnamed: IC3.3, R114.1
unnamed: IC3.7, R112.2
unnamed: IC3.51, R117.1
unnamed: J13.2, R80.1
unnamed: J14.2, R79.1
unnamed: JP1.1, R106.1
unnamed: L7.1, U2.34
unnamed: L8.1, U2.32
unnamed: L9.1, U3.21
unnamed: L10.1, U5.3
unnamed: L13.1, U21.7
unnamed: L13.2, R91.2, U21.2
unnamed: L14.1, U6.3
unnamed: L15.1, U7.7
unnamed: L15.2, U7.9
unnamed: Q6.3, R74.2
unnamed: Q7.3, R75.2
unnamed: R10.1, U2.68
unnamed: R16.2, U3.25
unnamed: R17.2, U3.26
unnamed: R18.2, U3.27
unnamed: R19.2, U3.28
unnamed: R23.1, U4.A8
unnamed: R24.1, U4.A5
unnamed: R28.2, U7.5
unnamed: R37.1, U1.AP36
unnamed: R38.1, U1.AR35
unnamed: R40.1, U1.AP35
unnamed: R41.1, U1.AP33
unnamed: R42.1, U1.AR33
unnamed: R43.1, U1.AR32
unnamed: R44.1, U1.AP32
unnamed: R62.2, U10.F6
unnamed: R64.1, R65.1, U8.K3
unnamed: R66.1, U13.C2
unnamed: R68.2, U13.J7
unnamed: R69.2, U13.H8
unnamed: R70.2, U13.J8
unnamed: R78.1, U17.3
unnamed: R93.2, U14.4
unnamed: R99.1, SW1.1
unnamed: R103.1, U6.5
unnamed: R104.2, R105.1, U6.6
unnamed: R111.2, U15.7
unnamed: R113.1, R115.1
unnamed: R113.2, U15.6
unnamed: R115.2, U15.5
unnamed: TP9.1, U1.T37
unnamed: U8.J7, Y4.3
unnamed: U10.F9, Y5.3
unnamed: U13.C6, U13.D6
unnamed: U19.3, U19.18, U19.43, U19.55, U19.113, U19.114, U19.116, U19.117, U19.140, U19.141, U19.142, U19.143, U19.144
RX_VOUT: C310.1, C311.1, C312.1, C317.1, C318.1, TP23.1, U13.D2, U13.E1, U13.E2, U13.E3, U13.F2, U14.1, U14.8, U14.11, U14.12, U14.13
VBAT: C149.1, D18.2, Q11.2, U7.1, U7.10
VBUS: Q11.1, R92.1
VCC0V6_DDR: C99.1, C100.1, C102.1, C103.1, C108.1, C110.1, C112.1, C114.1, C116.1, C118.1, C120.1, C122.1, C124.1, C125.1, C127.1, C129.1, C132.1, C134.1, C136.1, C138.1, C140.1, C142.1, C144.1, C147.1, L10.2, R23.2, R24.2, U4.AA3, U4.AA5, U4.AA8, U4.AA10, U4.B3, U4.B5, U4.B8, U4.B10, U4.D1, U4.D5, U4.D8, U4.D12, U4.F3, U4.F10, U4.U3, U4.U10, U4.W1, U4.W5, U4.W8, U4.W12, U5.6
VCC1V8_DDR: C106.1, C131.1, C146.1, C148.1, C260.1, C261.1, C262.1, C263.1, C264.1, C265.1, C266.1, C267.1, R25.2, R26.1, U4.F1, U4.F12, U4.G4, U4.G9, U4.T4, U4.T9, U4.U1, U4.U12
VCC3V3_EXT: C167.1, C169.1, C171.1, C173.1, C177.1, C183.1, C184.1, C225.1, J4.6, J5.6, J6.6, J8.6, R20.2, R56.2, R57.2, TP15.1, U11.6, U11.15, U17.1
VCC3V3_PMU: C40.1, C93.1, C218.1, D13.2, R9.1, R46.1, R48.1, R49.1, R50.1, R51.1, R52.1, R53.1, R60.1, R102.2, U2.31
VCC3V3_SD: C52.1, U2.58
VCCA1V8_IMAGE: C47.1, C152.1, C153.1, C156.1, C187.1, R32.2, R33.2, R36.2, R59.2, U2.6
VCCA1V8_PMU: C43.1, C214.1, C216.1, R26.2, U2.5
VCCA_1V8: C41.1, C213.1, C215.1, C241.1, C242.1, C244.1, C289.1, C290.1, R85.1, R86.1, R87.1, R88.1, U2.3, U10.J3, U10.J7
VCCIO6: C243.1, R84.2
VCCIO_ACODEC: C51.1, C259.1, U2.28
VCCIO_SD: C54.1, C240.1, U2.29
VCCIO_WL: C81.1, C82.1, C250.1, R8.1, R89.2, U3.22
VCC_1V8: C35.1, C36.1, C37.1, L3.1, R4.2, R84.1, R89.1
VCC_3V3: C55.1, C190.1, C226.1, C227.1, C228.1, C229.1, C230.1, C231.1, C232.1, C233.1, C245.1, D19.K, D20.2, D27.2, J2.P1, J2.P2, J2.P3, U2.55, U19.57, U19.58, U19.59, U19.60, U19.71
VCC_DDR: C46.1, C49.1, C57.1, C87.1, C88.1, C89.1, C90.1, C91.1, C92.1, C94.1, C95.1, C96.1, C97.1, C101.1, C104.1, C109.1, C111.1, C113.1, C115.1, C117.1, C119.1, C121.1, C123.1, C126.1, C128.1, C130.1, C133.1, C135.1, C137.1, C139.1, C141.1, C143.1, C145.1, L5.1, R6.1, R22.1, U2.26, U4.A4, U4.A9, U4.AB4, U4.AB9, U4.F5, U4.F8, U4.H1, U4.H5, U4.H8, U4.H12, U4.K1, U4.K3, U4.K10, U4.K12, U4.N1, U4.N3, U4.N10, U4.N12, U4.R1, U4.R5, U4.R8, U4.R12, U4.U5, U4.U8
VDDA0V9_IMAGE: C42.1, C151.1, C154.1, C155.1, C186.1, R31.2, R34.2, R35.2, R58.2, U2.23
VDDA0V9_PMU: C50.1, C210.1, C212.1, C217.1, C219.1, U2.20
VDDA_0V9: C44.1, C209.1, C211.1, C238.1, C239.1, U2.21
VDD_CPU: C10.1, C12.1, C15.1, C17.1, C19.1, C280.1, C281.1, C282.1, L14.2, R104.1, TP12.1
VDD_GPU: C2.1, C4.1, C6.1, C7.1, C9.1, C23.1, C25.1, C25.2, C29.1, C31.1, L1.1, R1.1, R1.2, U2.8
VDD_LOGIC: C11.1, C13.1, C14.1, C16.1, C18.1, C20.1, C21.1, C24.1, C26.1, C26.2, C30.1, C32.1, L2.1, R2.1, R2.2, R3.1
VDD_NPU: C1.1, C3.1, C5.1, C8.1, C45.1, C48.1, C53.1, C53.2, C56.1, L4.1, R5.1, R5.2, U2.64

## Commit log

2021-12-13 wifi module complete
2021-12-13 sata updated
2021-12-13 LPDDR3 SECTION COMPLETE
2021-12-13 littleupdate
2021-12-13 gps add
2021-12-14 added 3 screens
2021-12-16 all screens added_3 items left
2021-12-16 updated 4G module and simcard
2021-12-17 update NFC, 5G, GPS__left LiPo charger+screen changes
2021-12-20 schematic capture complete
2022-01-02 updated footprint and schematics
2022-01-02 update 1 extra hdmi to mipi interface
2022-01-02 complete update on schematic and all display interfaces
2022-01-02 complete update on schematiC + FOOTPRINT
2022-01-10 wireless power TX RX added
2022-01-10 added usb power output
2022-01-10 updates rules check and associations
2022-01-11 update schematic
2022-01-11 layout change
